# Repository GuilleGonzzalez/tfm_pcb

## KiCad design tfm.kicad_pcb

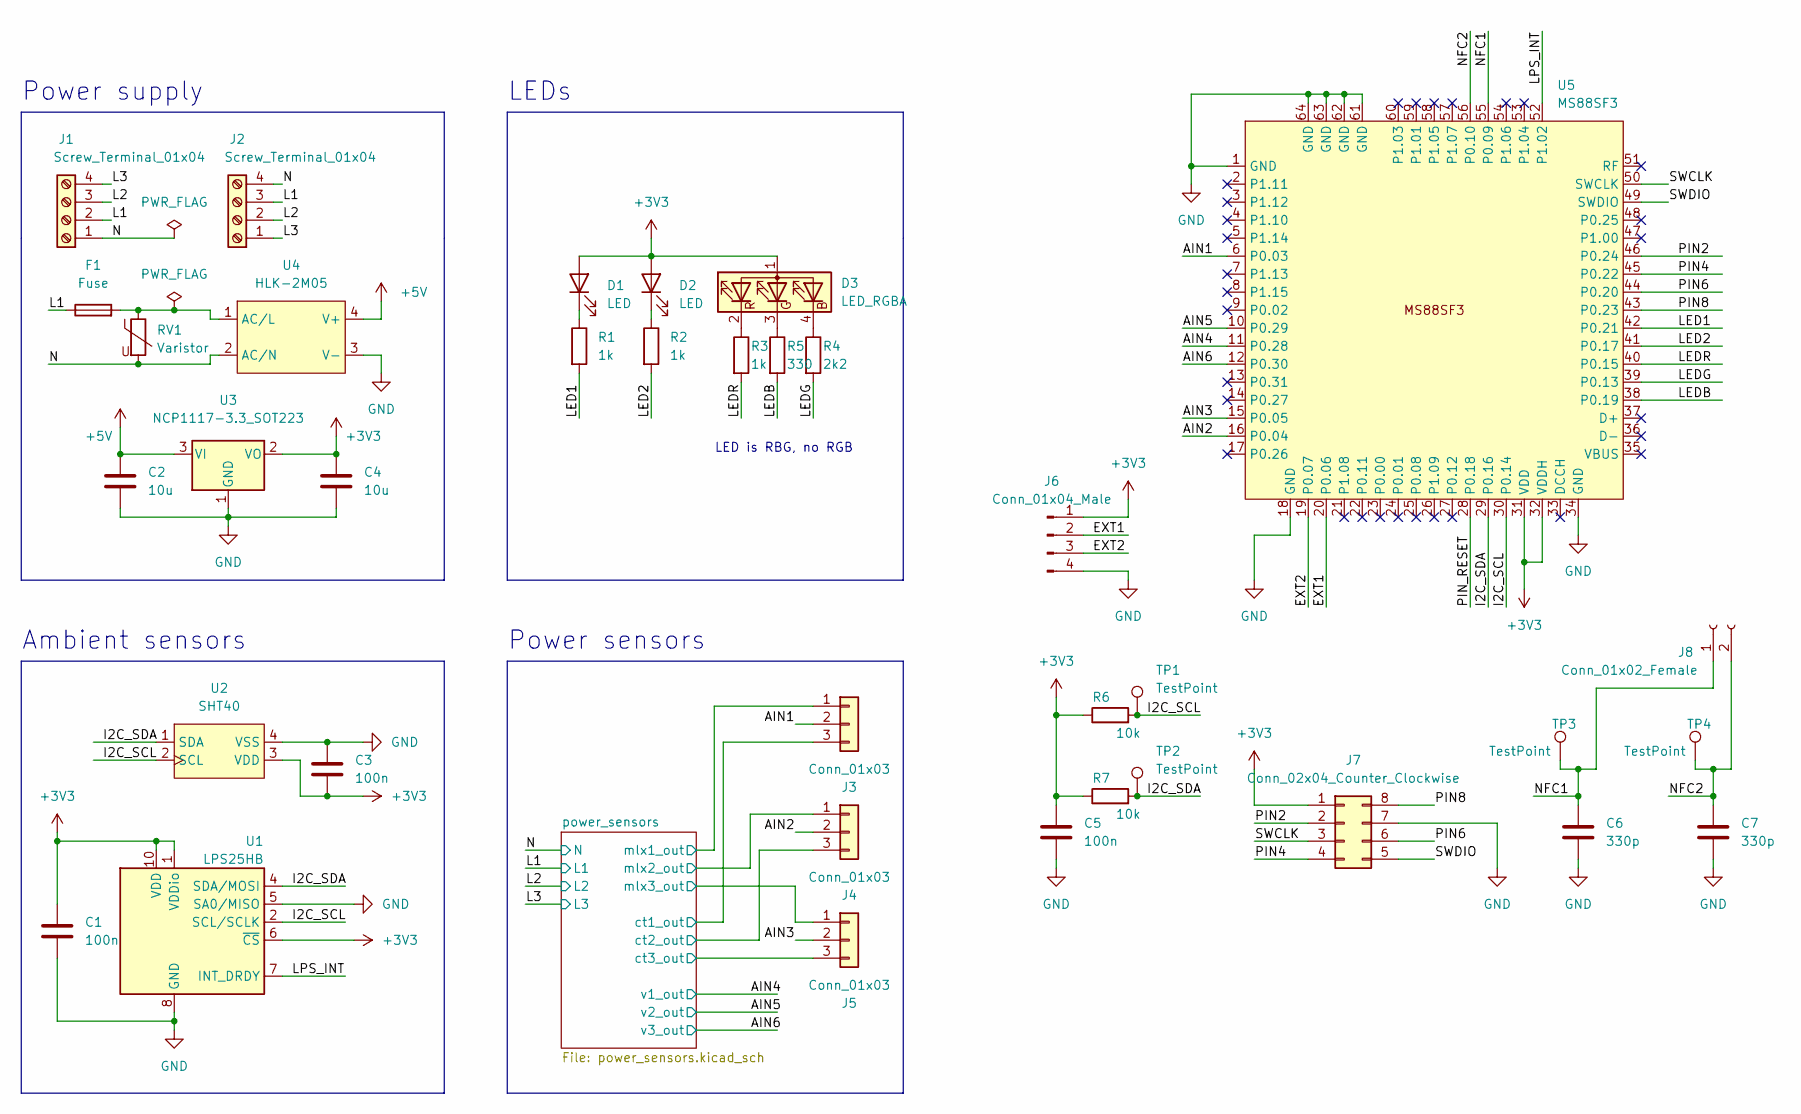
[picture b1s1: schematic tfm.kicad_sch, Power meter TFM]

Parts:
C1, C3, C5: 100n; C_0402_1005Metric
C2, C4: 10u; C_1206_3216Metric
C6, C7: 330p; C_0402_1005Metric
D1, D2: LED; LED_0402_1005Metric
D3: LED_RGBA; APHF1608LSEEQBDZGKC
F1: Fuse; Fuse_2512_6332Metric
J1, J2: Screw_Terminal_01x04; TerminalBlock_Altech_AK300-4_P5.00mm
J3, J4, J5: Conn_01x03; PinHeader_1x03_P2.54mm_Vertical
J6: Conn_01x04_Male; PinHeader_1x04_P2.54mm_Vertical
J7: Conn_02x04_Counter_Clockwise; PinSocket_2x04_P1.27mm_Vertical_SMD
J8: Conn_01x02_Female; PinHeader_1x02_P2.54mm_Vertical
R1, R2, R3: 1k; R_0402_1005Metric
R4: 2k2; R_0402_1005Metric
R5: 330; R_0402_1005Metric
R6, R7: 10k; R_0402_1005Metric
RV1: Varistor; RV_Disc_D12mm_W3.9mm_P7.5mm
TP1, TP2, TP3, TP4: TestPoint; TestPoint_Pad_D1.5mm
U1: LPS25HB; ST_HLGA-10_2.5x2.5mm_P0.6mm_LayoutBorder3x2y
U2: SHT40
U3: NCP1117-3.3_SOT223; SOT-223-3_TabPin2
U4: HLK-2M05
U5: MS88SF3

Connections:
+3V3: C1.1, C3.2, C4.1, C5.1, D1.2 (A), D2.2 (A), D3.1 (A), J6.1, J7.1, R6.1, R7.1, U1.1 (VDDio), U1.6 (~CS), U1.10 (VDD), U2.3 (VDD), U3.2 (VO), U5.31 (VDD), U5.32 (VDDH); also elsewhere on the board
+5V: C2.1, U3.3 (VI), U4.4 (V+); also elsewhere on the board
/AIN1: J3.2, U5.6 (P0.03)
/AIN2: J4.2, U5.16 (P0.04)
/AIN3: J5.2, U5.15 (P0.05)
/AIN4: U5.11 (P0.28); also elsewhere on the board
/AIN5: U5.10 (P0.29); also elsewhere on the board
/AIN6: U5.12 (P0.30); also elsewhere on the board
/EXT1: J6.2, U5.20 (P0.06)
/EXT2: J6.3, U5.19 (P0.07)
/I2C_SCL: R6.2, TP1.1, U1.2 (SCL/SCLK), U2.2 (SCL), U5.30 (P0.14)
/I2C_SDA: R7.2, TP2.1, U1.4 (SDA/MOSI), U2.1 (SDA), U5.29 (P0.16)
/L1: F1.1, J1.2, J2.3; also elsewhere on the board
/L2: J1.3, J2.2; also elsewhere on the board
/L3: J1.4, J2.1; also elsewhere on the board
/LED1: R1.2, U5.42 (P0.21)
/LED2: R2.2, U5.41 (P0.17)
/LEDB: R5.2, U5.38 (P0.19)
/LEDG: R4.2, U5.39 (P0.13)
/LEDR: R3.2, U5.40 (P0.15)
/LPS_INT: U1.7 (INT_DRDY), U5.52 (P1.02)
/N: J1.1, J2.4, RV1.2, U4.2 (AC/N); also elsewhere on the board
/NFC1: C6.1, J8.1, TP3.1, U5.55 (P0.09)
/NFC2: C7.1, J8.2, TP4.1, U5.56 (P0.10)
/PIN2: J7.2, U5.46 (P0.24)
/PIN4: J7.4, U5.45 (P0.22)
/PIN6: J7.6, U5.44 (P0.20)
/PIN8: J7.8, U5.43 (P0.23)
/PIN_RESET: U5.28 (P0.18)
/SWCLK: J7.3, U5.50 (SWCLK)
/SWDIO: J7.5, U5.49 (SWDIO)
/power_sensors/ct1_out: J3.3; also elsewhere on the board
/power_sensors/ct2_out: J4.3; also elsewhere on the board
/power_sensors/ct3_out: J5.3; also elsewhere on the board
/power_sensors/mlx1_out: J3.1; also elsewhere on the board
/power_sensors/mlx2_out: J4.1; also elsewhere on the board
/power_sensors/mlx3_out: J5.1; also elsewhere on the board
GND: C1.2, C2.2, C3.1, C4.2, C5.2, C6.2, C7.2, J6.4, J7.7, U1.3 (GND), U1.5 (SA0/MISO), U1.8 (GND), U1.9 (GND), U2.4 (VSS), U3.1 (GND), U4.3 (V-), U5.1 (GND), U5.18 (GND), U5.34 (GND), U5.61 (GND), U5.62 (GND), U5.63 (GND), U5.64 (GND); also elsewhere on the board
unnamed: D1.1 (K), R1.1
unnamed: D2.1 (K), R2.1
unnamed: D3.2 (RK), R3.1
unnamed: D3.4 (BK), R4.1
unnamed: F1.2, RV1.1, U4.1 (AC/L)
unnamed: D3.3 (GK), R5.1

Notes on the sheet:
Power supply
Power sensors
Ambient sensors
LED is RBG, no RGB
LEDs

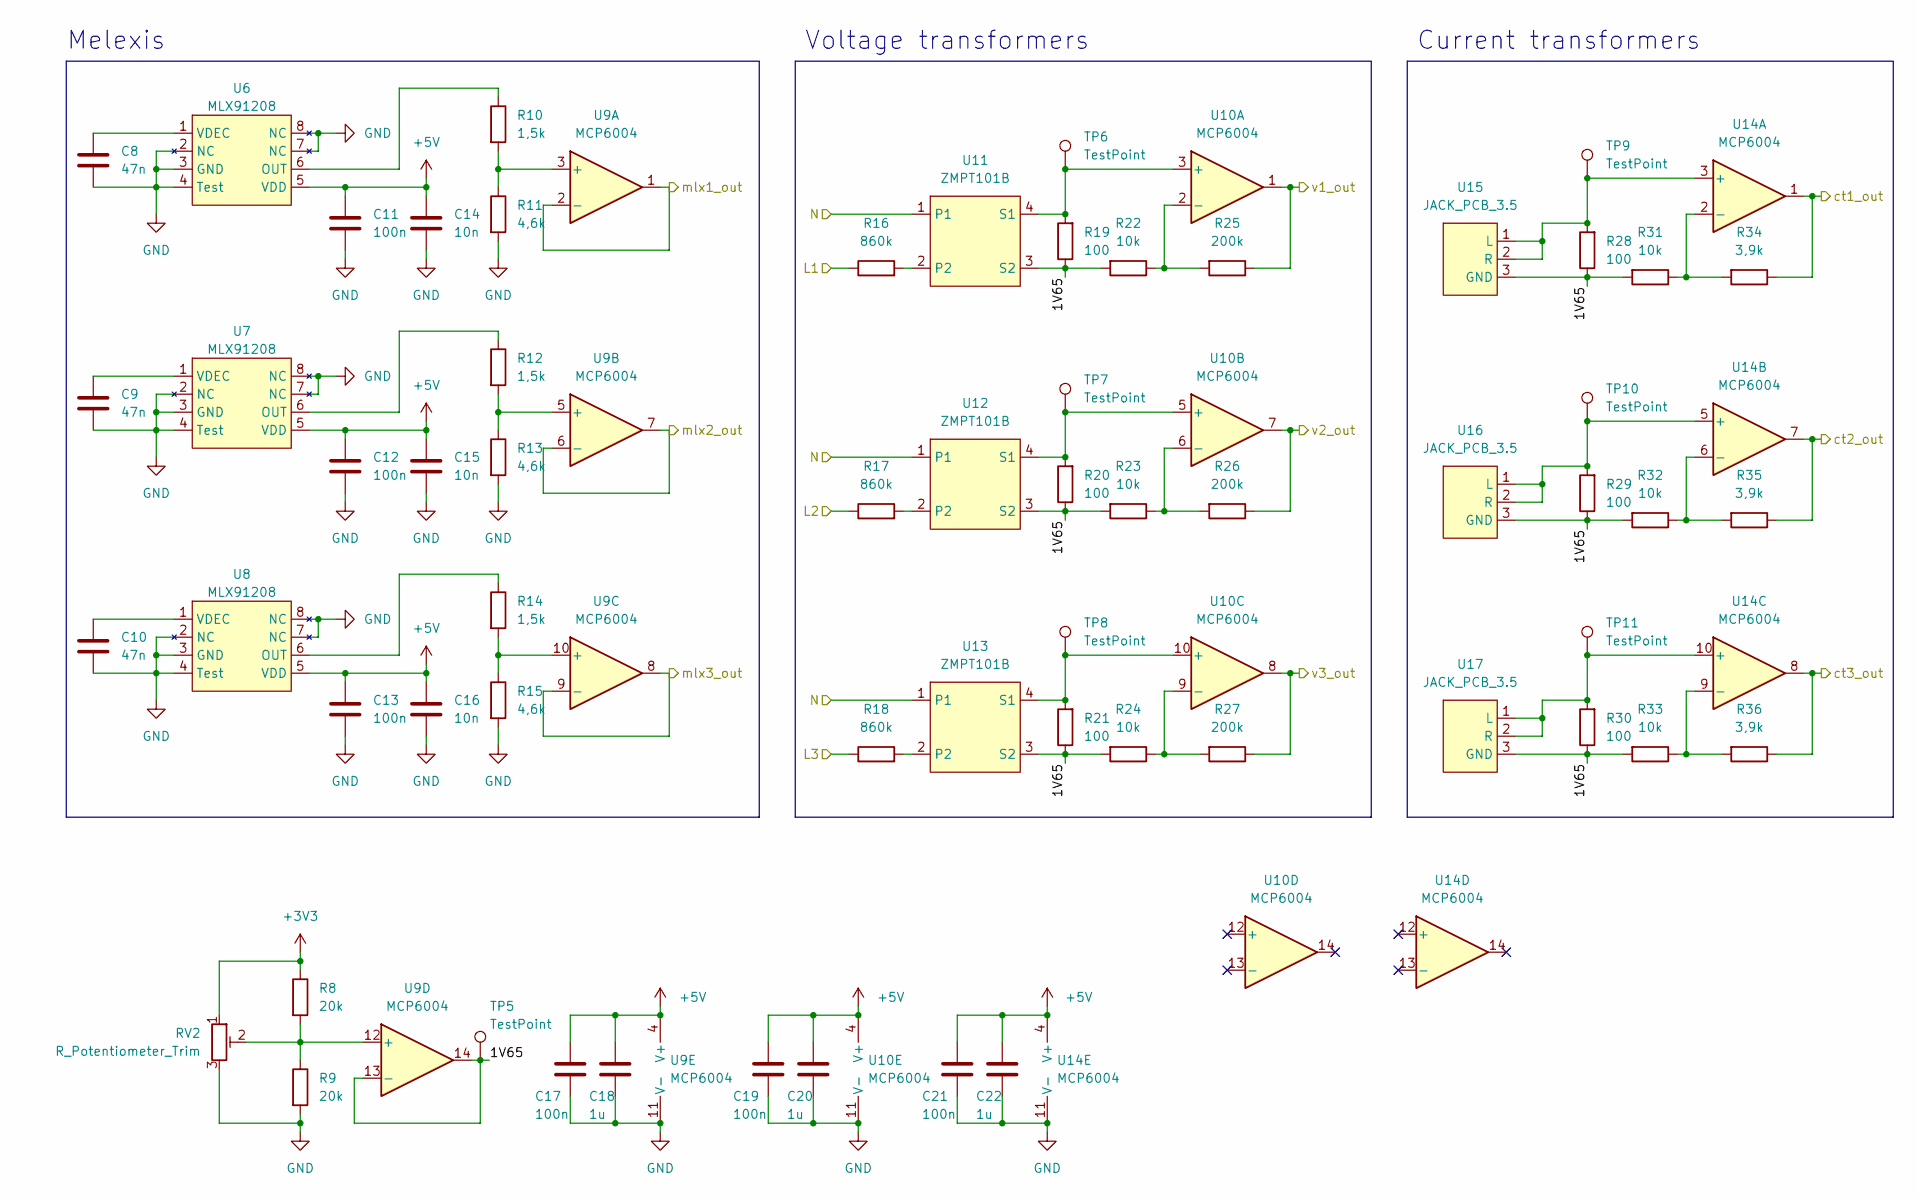
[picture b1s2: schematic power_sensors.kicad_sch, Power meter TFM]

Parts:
C8, C9, C10: 47n; C_0402_1005Metric
C11, C12, C13, C17, C19, C21: 100n; C_0402_1005Metric
C14, C15, C16: 10n; C_0402_1005Metric
C18, C20, C22: 1u; C_0402_1005Metric
R8, R9: 20k; R_0402_1005Metric
R10, R12, R14: 1,5k; R_0402_1005Metric
R11, R13, R15: 4,6k; R_0402_1005Metric
R16, R17, R18: 860k; R_Axial_DIN0207_L6.3mm_D2.5mm_P7.62mm_Horizontal
R19, R20, R21, R28, R29, R30: 100; R_0402_1005Metric
R22, R23, R24, R31, R32, R33: 10k; R_0402_1005Metric
R25, R26, R27: 200k; R_0402_1005Metric
R34, R35, R36: 3,9k; R_0402_1005Metric
RV2: R_Potentiometer_Trim; Potentiometer_Bourns_3296W_Vertical
TP5, TP6, TP7, TP8, TP9, TP10, TP11: TestPoint; TestPoint_Pad_D1.5mm
U6, U7, U8: MLX91208; MLX91208_USHIELD
U9, U10, U14: MCP6004; TSSOP-14_4.4x5mm_P0.65mm
U11, U12, U13: ZMPT101B
U15, U16, U17: JACK_PCB_3.5

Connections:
+3V3: R8.1, RV2.1; also elsewhere on the board
+5V: C11.1, C12.1, C13.1, C14.1, C15.1, C16.1, C17.1, C18.1, C19.1, C20.1, C21.1, C22.1, U6.5 (VDD), U7.5 (VDD), U8.5 (VDD), U9.4 (V+), U10.4 (V+), U14.4 (V+); also elsewhere on the board
/AIN4: R25.1, U10.1; also elsewhere on the board
/AIN5: R26.1, U10.7; also elsewhere on the board
/AIN6: R27.1, U10.8; also elsewhere on the board
/L1: R16.1; also elsewhere on the board
/L2: R17.1; also elsewhere on the board
/L3: R18.1; also elsewhere on the board
/N: U11.1, U12.1, U13.1; also elsewhere on the board
/power_sensors/1V65: R19.1, R20.1, R21.1, R22.2, R23.2, R24.2, R28.1, R29.1, R30.1, R31.2, R32.2, R33.2, TP5.1, U9.13 (-), U9.14, U11.3 (S2), U12.3 (S2), U13.3 (S2), U15.3 (GND), U16.3 (GND), U17.3 (GND)
/power_sensors/ct1_out: R34.1, U14.1; also elsewhere on the board
/power_sensors/ct2_out: R35.1, U14.7; also elsewhere on the board
/power_sensors/ct3_out: R36.1, U14.8; also elsewhere on the board
/power_sensors/mlx1_out: U9.1, U9.2 (-); also elsewhere on the board
/power_sensors/mlx2_out: U9.6 (-), U9.7; also elsewhere on the board
/power_sensors/mlx3_out: U9.8, U9.9 (-); also elsewhere on the board
GND: C8.2, C9.2, C10.2, C11.2, C12.2, C13.2, C14.2, C15.2, C16.2, C17.2, C18.2, C19.2, C20.2, C21.2, C22.2, R9.2, R11.2, R13.2, R15.2, RV2.3, U6.2 (NC), U6.3 (GND), U6.4 (Test), U6.7 (NC), U6.8 (NC), U7.2 (NC), U7.3 (GND), U7.4 (Test), U7.7 (NC), U7.8 (NC), U8.2 (NC), U8.3 (GND), U8.4 (Test), U8.7 (NC), U8.8 (NC), U9.11 (V-), U10.11 (V-), U14.11 (V-); also elsewhere on the board
unnamed: C8.1, U6.1 (VDEC)
unnamed: C9.1, U7.1 (VDEC)
unnamed: C10.1, U8.1 (VDEC)
unnamed: R8.2, R9.1, RV2.2, U9.12 (+)
unnamed: R10.1, U6.6 (OUT)
unnamed: R10.2, R11.1, U9.3 (+)
unnamed: R12.1, U7.6 (OUT)
unnamed: R12.2, R13.1, U9.5 (+)
unnamed: R14.1, U8.6 (OUT)
unnamed: R14.2, R15.1, U9.10 (+)
unnamed: R16.2, U11.2
unnamed: R17.2, U12.2
unnamed: R18.2, U13.2
unnamed: R19.2, TP6.1, U10.3 (+), U11.4 (S1)
unnamed: R20.2, TP7.1, U10.5 (+), U12.4 (S1)
unnamed: R21.2, TP8.1, U10.10 (+), U13.4 (S1)
unnamed: R22.1, R25.2, U10.2 (-)
unnamed: R23.1, R26.2, U10.6 (-)
unnamed: R24.1, R27.2, U10.9 (-)
unnamed: R28.2, TP9.1, U14.3 (+), U15.1 (L), U15.2 (R)
unnamed: R29.2, TP10.1, U14.5 (+), U16.1 (L), U16.2 (R)
unnamed: R30.2, TP11.1, U14.10 (+), U17.1 (L), U17.2 (R)
unnamed: R31.1, R34.2, U14.2 (-)
unnamed: R32.1, R35.2, U14.6 (-)
unnamed: R33.1, R36.2, U14.9 (-)

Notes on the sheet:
Voltage transformers
Melexis
Current transformers

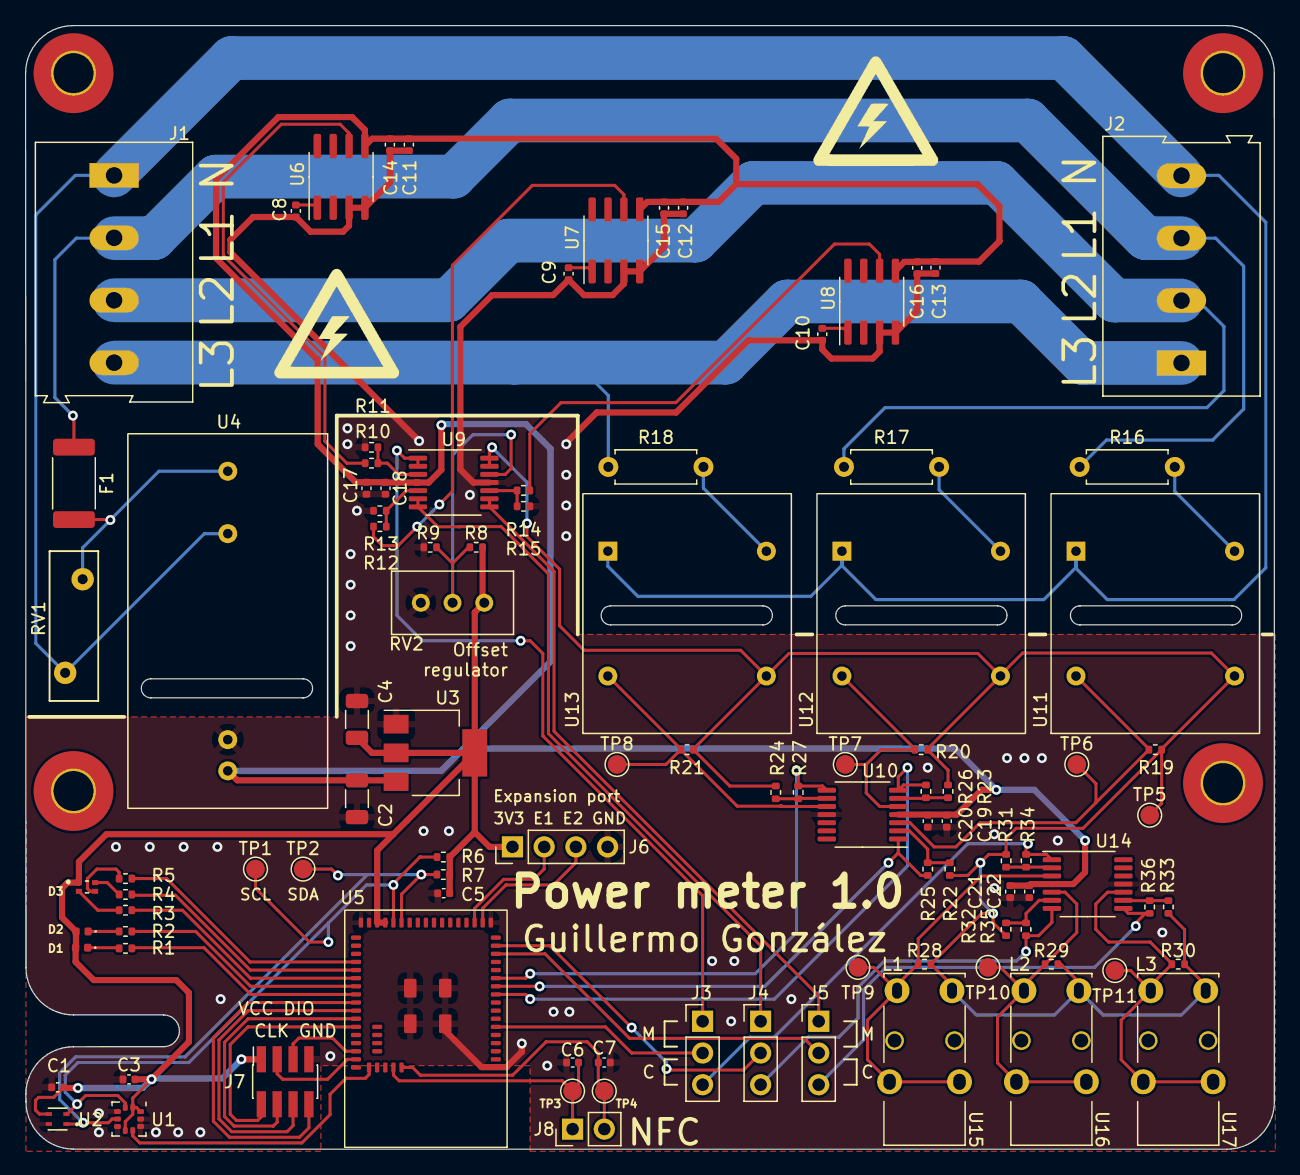
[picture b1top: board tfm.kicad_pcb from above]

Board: 2 copper layers, 100.0 x 90.0 mm, 100 parts (0 on the bottom side), 69 nets.

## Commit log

2022-04-29 Add files
2022-04-29 Add guille_library
2022-04-29 Fix DRC warnings
2022-04-29 Edge cuts with curves
2022-04-30 Fix jack orientation and add 3d model
2022-05-03 Minor changes
2022-05-03 Uodate schematic with NFC header
2022-05-03 Change libraries path
2022-05-03 Fix PCB warnings
2022-05-03 Remove tfm1 project
2022-05-03 Update 3d references and add testpoints
2022-05-03 Update 3d footprints references
2022-05-03 Fix 3d footprints again
2022-05-03 Add vias for ground planes
2022-05-03 Fix MLX 3d
2022-05-05 Update jack footprint and add texts
2022-05-05 Add decoupling capacitors, expansion port and test ponits
2022-05-05 Add outputs
2022-05-27 Fix divider and leds after board tested
2022-09-16 Last Power Meter 1.0 commit
